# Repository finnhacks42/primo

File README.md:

KinderBot
=====

Contains design files and code for my version of the Primo robotic platform for young kids www.primo.io licenced under CC by-nc-sa 4.0 International
## Components
### Board
   - laser cut xxx and yyy in 3mm ply or bamboo
   - laser cut zzz in 1.5mm clear acrylic
   - 3d print 4 off zzz
   - 1 colorsense PCB
   - Arduino mega
   - HC05 serial bluetooth module
   - 16 rgb leds
   - 16 red leds

### Robot
   - Kinder surprise egg
   - laser cut zzz of 3mm ply
   - Arduino pro micro 
   - 2 gear motors 3-6V with tyres
   - HC05 serial bluetooth module
   - H-Bridge IC (sn75441one)
   - 1.1K resistor
   - 1.2K resistor
   - 2 12pin female header
   - 2 2pin male header
   - Battery holder for 4xAA

## Pairing Bluetooth modules
Once you have all your components ready, the first step set up the two HC-05 bluetooth modules to automatically pair with one another when they are turned on. We do this now as it is easier to setup and debug with both Arduinos handy than when they are plugged into the board/robot. We will configure the module for the board as the master and the module for the robot as the slave. 

   1) Get a permanent marker and write S for slave on one module and M for master on the other. Do it now, trust me, otherwise you will configure them and then forget which is which.
   2) Using the Arduino pro-micro for your bot, construct the circuit below on a breadboard.

Note that different manufacturers of the HC-05 breakout boards have used slightly different variants of pin orderings. On my board they `key` pin is not broken out. To temporally pull it high while programming the chip in AT mode I have just wedged a jumper wire under the protective plastic coating. Alternatively you can solder a wire directly to the pad on the bluetooth chip (see image below).

   3) Load the [bluetooth setup script](/code/bluetooth/bluetoothSetup/bluetoothSetup.ino) onto the arduino and open the serial monitor. If all goes well you should get an output like this:
   
   4) Copy the address of the slave into a text editor and replace all : with ,
   
   5) Unplug the arduino and swap the position of the master and slave modules. Edit the bluetooth setup script to setup the master module and re-upload the script to the arduino. Again if all goes well you should see ...
   
### Debugging
The bluetooth modules are setup by first putting them in AT mode and then sending AT commands to configure them. The script simply sends AT commands from the Arduino to the bluetooth module. If the steps above did not work ...
   1) Check if the module is in AT mode. If the module being configured (the one closest to the breadboard) is sucessfully in AT mode it should be flashing slowly ~ once per second when powered. If both modules are flashing rapidly, double check the wiring to the key pin. Ensure that the key pin is connected before you power up the module. 
   2) If the module is flashing slowly but you get nothing back from the AT commands check that RX/TX are wired correctly. TX0 on the arduino should be connected to RX on the bluetooth and RX0 on the arduino to TX on the bluetooth module.
   3) If the module is flashing slowly but you get garbage printed in the serial monitor, check that you serial termial baud rate is set to 9600 and line ending to NL & CR.
   4) If the module is flashing slowly but some AT command errors try running the script again. If that fails you may have to experiment with a different sequence of AT commands see xxx for an explaination of AT codes. 

## Assembly

### Board

### Robot

## Programming & Calibration

### Board

### Robot

We now need to

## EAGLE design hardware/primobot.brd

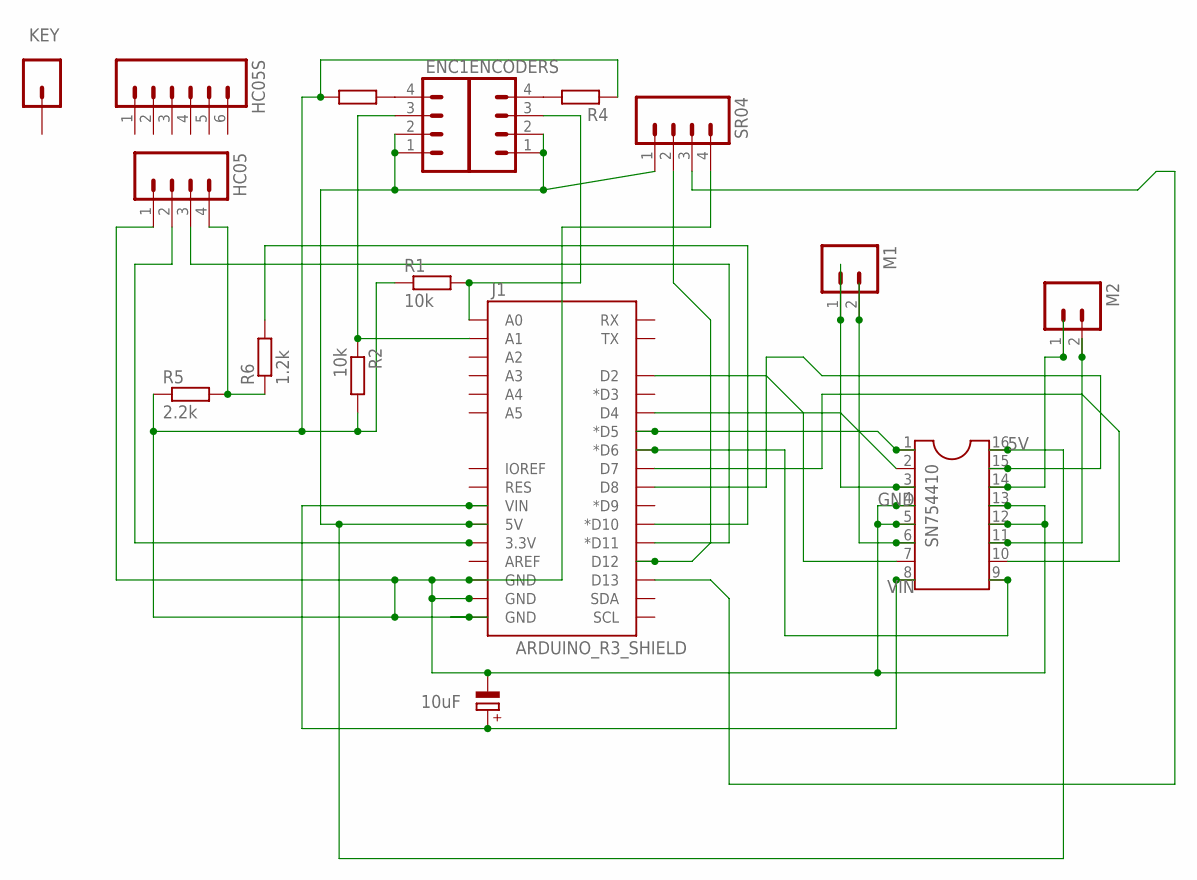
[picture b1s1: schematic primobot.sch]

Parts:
C1: 10uF; E5-10,5
ENC1: M04PTH; 1X04
ENCODERS: M04PTH; 1X04
HC05: M04PTH; 1X04
HC05S: M06SILK_FEMALE_PTH; 1X06
J1: ARDUINO_R3_SHIELD; UNO_R3_SHIELD
KEY: M01PTH; 1X01
M1, M2: M02PTH; 1X02
R1, R2: 10k; 0207/10
R3, R4: R-EU_0207/10; 0207/10
R5: 2.2k; 0207/10
R6: 1.2k; 0207/10
SN754410: DIL16S; SOCKET-16
SR04: M04PTH; 1X04

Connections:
5V: ENC1.1, ENC1.2, ENCODERS.1, ENCODERS.2, J1.5V, SN754410.16, SR04.1
GND: C1.-, HC05.1, J1.GND@0 (GND), J1.GND@1 (GND), J1.GND@2 (GND), R1.1, R2.2, R3.1, R4.1, R5.1, SN754410.4, SN754410.5, SN754410.12, SN754410.13, SR04.4
unnamed: J1.D5 (*D5), SN754410.1
unnamed: M1.2, SN754410.6
unnamed: M1.1, SN754410.3
unnamed: J1.D13, SR04.3
unnamed: M2.1, SN754410.14
unnamed: M2.2, SN754410.11
unnamed: J1.D7, SN754410.10
unnamed: HC05.2, J1.3.3V
unnamed: J1.D2, SN754410.7
unnamed: J1.D8, SN754410.15
unnamed: HC05.3, J1.D11 (*D11)
unnamed: J1.D6 (*D6), SN754410.9
unnamed: HC05.4, R5.2, R6.1
unnamed: J1.D10 (*D10), R6.2
unnamed: ENCODERS.4, R4.2
unnamed: ENC1.4, R3.2
unnamed: ENCODERS.3, J1.A0, R1.2
unnamed: ENC1.3, J1.A1, R2.1
unnamed: J1.D4, SN754410.2
unnamed: J1.D12, SR04.2
VIN: C1.+, J1.VIN, SN754410.8

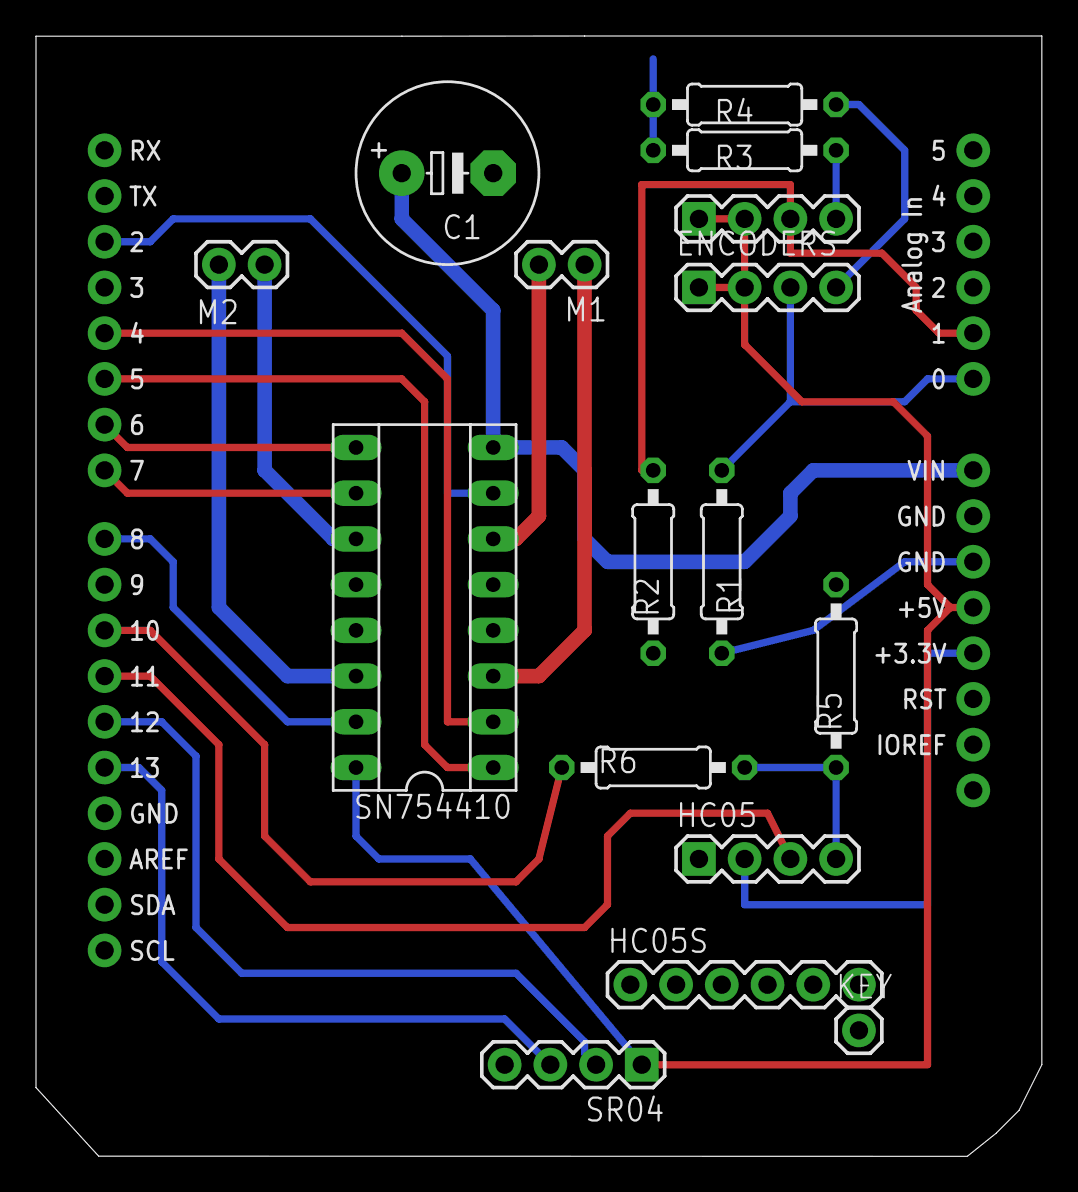
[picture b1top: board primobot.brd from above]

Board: 2 copper layers, 55.9 x 62.2 mm, 17 parts (0 on the bottom side), 23 nets.

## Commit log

2014-12-01 adds svg degin files for board
2014-12-01 enlarges space for resistor in programming tiles
2014-12-19 adds primo board code with median calculation. There is a bug in array access
2014-12-20 creates directory structure and adds code scripts for testing bluetooth communication
2014-12-20 gets primoboard codeto the point where leds light when tiles are inserted, code is executed when button is pushed and leds indicate which opperation is currently being executed. instruction execution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
2014-12-21 updates promoboard to where I thought it was on last commit
2014-12-21 adds first version of code for robot - just recieves instructions from board over bluetooth and prints them to Serial
2015-02-05 lots of changes
2015-02-14 too many changes to remember
2015-02-14 state when board was cncd
2015-02-22 prior to starting over on cnc board
2015-03-19 round 2 of board design
2015-03-21 state when board sent to manufacture
2015-05-04 updated svgs to fit manufactured board. Reconnected resistors in schematica
2015-05-04 adds code to test pcb from arduino sketchbook
2015-10-23 updates to printed circuit board. Still missing programming access, switch mount and charging access
2015-11-07 changes from old laptop
2015-11-07 fixes indicator test so LEDs come on in board order
2015-11-07 Updates RGBLEDTest to pins for printed PCB
2015-11-07 adds LDRTest, configured for printed pcb
2015-11-07 adds README for board callibration
2015-11-21 moves some common code to utils
2015-11-24 completes refactor of readdata.py and utils.py to avoid use of numpy/scipy
2015-11-24 removed old files
2015-11-24 moves things into a more logical directory structure
2018-04-01 updates board svg top to have tiles go all the same direction
2018-04-01 makes square pegs for board holder to glue in
2018-04-02 removes double cut from tiles in second row
2018-04-02 splits board design into 600 by 400 mm sheets
2018-04-11 adds .csv to gitignore
2018-04-11 adds bottom half of tile smaller than hole dimension
2018-04-11 adds cutout for switch and power in
2018-04-11 improves design to attach bottom of board
2018-04-11 adds version of board with cross support for pcb
2018-04-11 cleans up board design files
2018-04-11 cleans up svgs for robot
2018-04-13 completes robot design, adds cross support for pcb
2018-04-13 major updates to color sensing code
2018-04-15 moves axel back
2018-04-15 removes cable port
2018-04-15 moves mount point for kinder backward
2018-04-15 fixes cutout for switch
2018-04-15 adds script to test wheels on robot
2018-04-17 adds arduino sketch to pair hc05 bluetooth modules
2018-04-17 starts on docs, cleans up old stuff
2018-04-17 resizes images
2019-12-08 adds README for board setup
2019-12-08 cleans up board code
2019-12-08 cleans up notebook
2019-12-08 updates to include arduino code generation in read.py
2019-12-08 updates README
2019-12-08 local changes made oh so long ago
2019-12-08 adds initial readme for the robot section

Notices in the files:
parts and their libraries:
SparkFun-Connectors: Licensing: Creative Commons ShareAlike 4.0 International - https://creativecommons.org/licenses/by-sa/4.0
